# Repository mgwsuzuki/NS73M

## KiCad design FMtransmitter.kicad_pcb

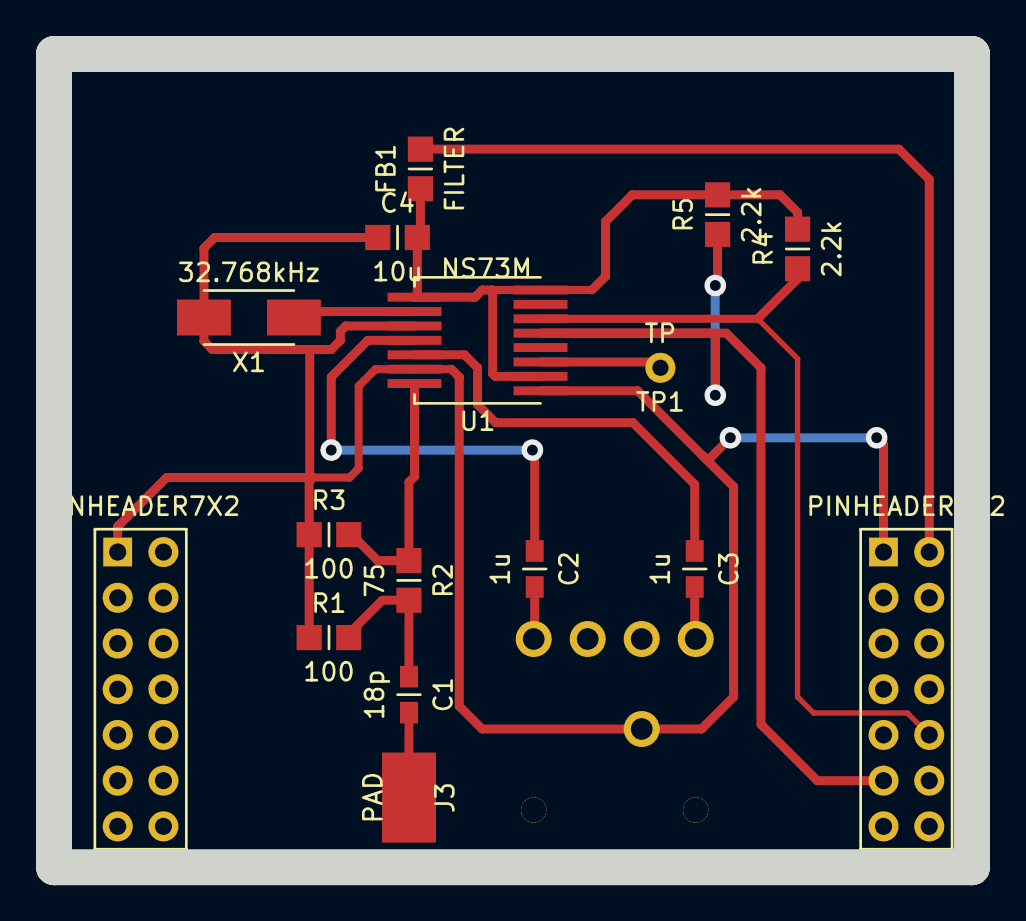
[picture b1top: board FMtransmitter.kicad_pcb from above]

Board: 2 copper layers, 51.0 x 45.2 mm, 17 parts (1 on the bottom side), 14 nets.

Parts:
C1: 18p; SMD_1608
C2, C3: 1u; SMD_1608
C4: 10u; SMD_2012
FB1: FILTER; SMD_2012
J1: MJ-2035
J2, J4: PINHEADER7X2; PINHEADER7x2
J3: PAD; PAD3x5
R1, R3: 100; SMD_2012
R2: 75; SMD_2012
R4, R5: 2.2k; SMD_2012
TP1: TP; TH1
U1: NS73M
X1: 32.768kHz; C6X060

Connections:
/SCL: J2.11, R5.2, U1.5
/SDA: J2.10, R4.2, U1.6
GND: C4.2, J1.5, J2.1, J4.1, R1.2, R3.2, U1.1, U1.11, U1.14, X1.1
unnamed: FB1.1, J2.2
unnamed: C1.1, J3.1
unnamed: C3.1, J1.1
unnamed: C2.1, J1.4
unnamed: C1.2, R1.1, R2.1
unnamed: C2.2, U1.12
unnamed: C3.2, U1.13
unnamed: C4.1, FB1.2, R4.1, R5.1, U1.2, U1.8, U1.9
unnamed: U1.10, X1.2
unnamed: R2.2, R3.1, U1.15
unnamed: TP1.1, U1.3

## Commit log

2014-07-23 add files
